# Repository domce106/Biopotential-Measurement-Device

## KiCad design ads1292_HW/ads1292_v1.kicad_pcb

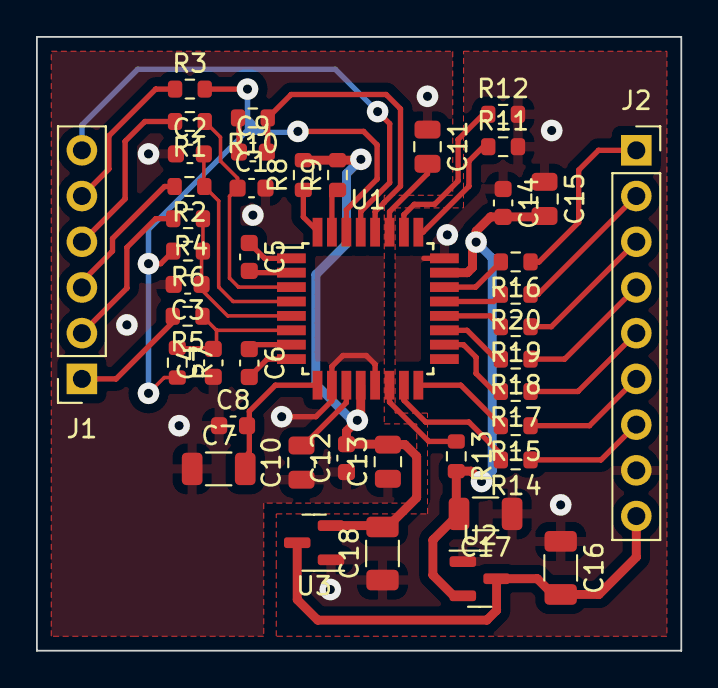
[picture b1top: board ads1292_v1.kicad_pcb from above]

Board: 2 copper layers, 35.8 x 34.1 mm, 44 parts (1 on the bottom side), 43 nets.

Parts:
C1, C2, C3, C4: 1nF; C_0603_1608Metric
C5, C6: 4.7nF; C_0603_1608Metric
C7, C16, C17, C18: 10uF; C_1206_3216Metric
C8, C12, C14: 100nF; C_0603_1608Metric
C9: 1.5nF; C_0603_1608Metric
C10, C11, C13, C15: 1uF; C_0805_2012Metric
J1: Conn_01x06_Female; PinSocket_1x06_P2.54mm_Vertical
J2: Digital; PinSocket_1x09_P2.54mm_Vertical
R1, R2, R3, R4, R5: 100k; R_0603_1608Metric
R6, R7: 10M; R_0603_1608Metric
R8, R9, R11, R12, R13: 10k; R_0603_1608Metric
R10: 1M; R_0603_1608Metric
R14, R15, R16, R17, R18, R19, R20: 100R; R_0603_1608Metric
R21: 0R; R_0603_1608Metric
U1: ADS1292-TQFP-32; TQFP-32_7x7mm_P0.8mm
U2, U3: MCP1703A-1202_SOT23; SOT-23

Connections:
AVDD: C12.2, C13.2, C18.2, R8.2, R9.2, U1.12 (AVDD), U3.2 (VO)
CS: J2.5, R17.1
DIN: J2.4, R18.1
DOUT: J2.2, R20.1
DRDY: J2.1, R16.1
DVDD: C14.2, C15.2, C17.2, R13.2, U1.23 (DVDD), U2.2 (VO)
Electrode_1_1: J1.4, R1.2
Electrode_1_2: J1.3, R2.2
Electrode_2_1: J1.2, R4.2
Electrode_2_2: J1.1, R5.2
GNDA: C1.2, C2.1, C3.2, C4.1, C7.1, C8.1, C10.1, C11.1, C12.1, C13.1, R21.2, U1.10 (VREFN), U1.13 (AVSS)
GNDD: C14.1, C15.1, C16.1, C17.1, C18.1, J2.8, R11.2, R12.2, R21.1, U1.24 (DGND), U2.1 (GND), U3.1 (GND)
IN1N: C1.1, R1.1, U1.3 (IN1N)
IN1P: C2.2, R2.1, U1.4 (IN1P)
IN2N: C3.1, R4.1, R6.1, U1.5 (IN2N)
IN2P: C4.2, R5.1, R7.1, U1.6 (IN2P)
unnamed: C5.1, U1.1 (PGA1N)
unnamed: C5.2, U1.2 (PGA1P)
unnamed: C6.1, U1.7 (PGA2N)
unnamed: C6.2, U1.8 (PGA2P)
unnamed: C7.2, C8.2, U1.9 (VREFP)
unnamed: C9.2, R10.1, U1.28 (RLDINV)
unnamed: C10.2, U1.11 (VCAP1)
unnamed: C11.2, U1.27 (VCAP2)
unnamed: J1.5, R3.1
unnamed: R8.1, U1.32 (IN3N)
unnamed: R9.1, U1.31 (IN3P)
unnamed: R11.1, U1.25 (GPIO2)
unnamed: R12.1, U1.26 (GPIO1)
unnamed: R13.1, U1.14 (CLKSEL)
unnamed: R14.2, U1.15 (~PWND/RESET)
unnamed: R15.2, U1.16 (START)
unnamed: R16.2, U1.22 (~DRDY)
unnamed: R17.2, U1.18 (~CS)
unnamed: R18.2, U1.19 (DIN)
unnamed: R19.2, U1.20 (SCLK)
unnamed: R20.2, U1.21 (DOUT)
PWND/RESET: J2.7, R14.1
RLD: C9.1, R3.2, R6.2, R7.2, R10.2, U1.30 (RLDOUT)
SCLK: J2.3, R19.1
START: J2.6, R15.1
Test: J1.6, U1.29 (RLDIN/RLDREF)
VCC: C16.2, J2.9, U2.3 (VI), U3.3 (VI)

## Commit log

2024-05-21 Commit all code and files
